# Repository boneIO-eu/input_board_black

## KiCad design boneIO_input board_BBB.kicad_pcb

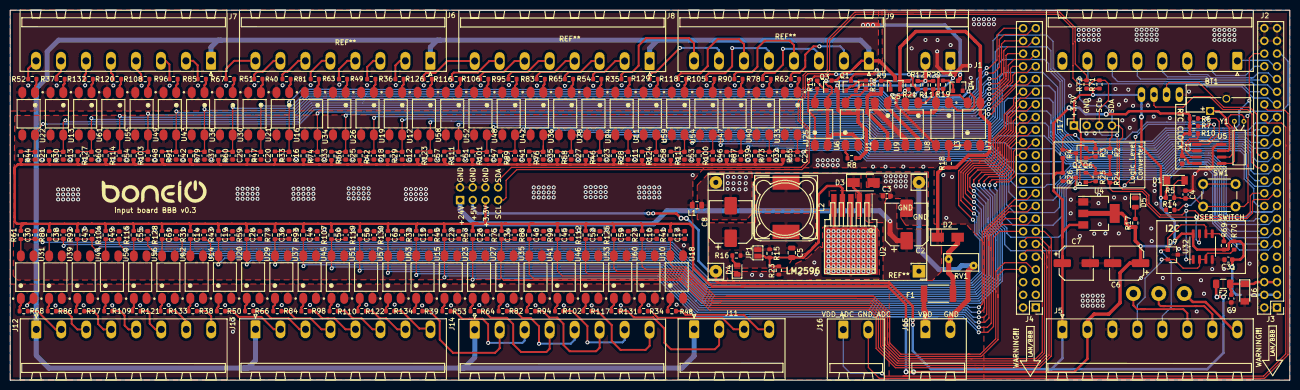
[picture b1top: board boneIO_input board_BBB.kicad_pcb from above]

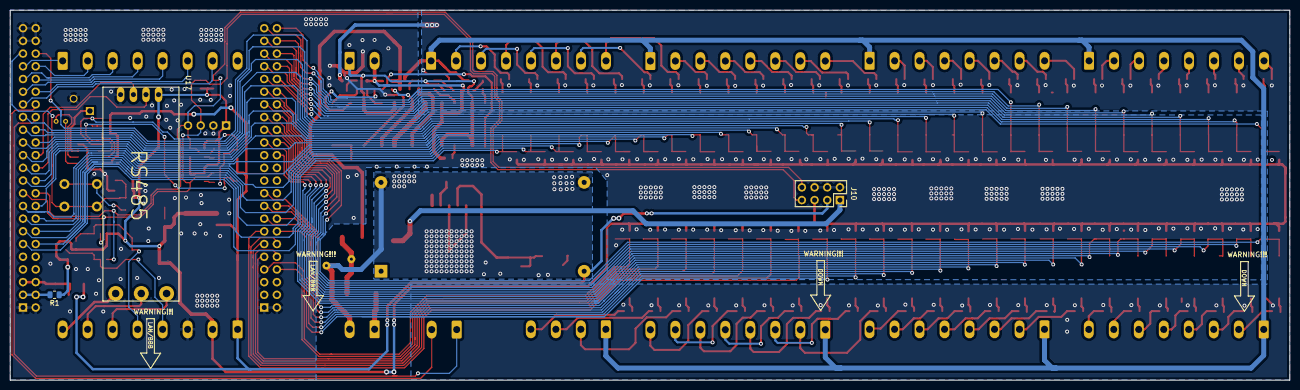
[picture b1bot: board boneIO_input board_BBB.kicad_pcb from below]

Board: 2 copper layers, 256.0 x 74.0 mm, 298 parts (3 on the bottom side), 215 nets.

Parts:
BT1: Battery; Battery_Panasonic_CR1220-VCN_Vertical_CircularHoles
C1, C4, C9, C10, C11, C12, C13, C14, C15, C16, C17, C18, C19, C20, C21, C22, C23, C24, C25, C26, C27, C28, C29, C30, C31, C32, C33, C34, C35, C36, C37, C38, C39, C40, C41, C42, C43, C44, C45, C46, C47, C48, C49, C50, C51, C52, C53, C54, C55, C56, C57, C58, C59, C60, C61, C62: 100n; C_0603_1608Metric
C2: 100uF/50V; CP_Elec_8x10
C3: 100n_NC; C_0603_1608Metric
C5: 3n3; C_0805_2012Metric
C6, C7: 100uF/16V; CP_Elec_6.3x5.4
C8: 220u/35V; CP_Elec_8x10
D1: 1N4148; D_MiniMELF
D2, D3: SS34; D_SMA
D4: LED_RED_NC; LED_0805_2012Metric
D5: LED_RED; LED_0805_2012Metric
D6: 5V6; D_MiniMELF
D7: BAT54A; SOT-23
F1: Fuse_3A; Fuse_2512_6332Metric
F2: 500mA; Fuse_1206_3216Metric
J1: EXT_PSU; PhoenixContact_MSTBA_2,5_2-G_1x02_P5.00mm_Horizontal
J2, J5, J6, J7, J8, J9, J12, J13, J14: Screw_Terminal_01x08; 8pin
J3, J4: BeagleBone_Black_Header; PinHeader_2x23_P2.54mm_Vertical
J10: Conn_02x04_Odd_Even; PinSocket_2x04_P2.54mm_Vertical
J11: Screw_Terminal_01x04; Phoenix_1x04_P5.00mm_Horizontal
J15, J16: Screw_Terminal_01x02; Phoenix_1x02_P5.00mm_Horizontal
J17: OLED; PinSocket_1x04_P2.54mm_Vertical
JP1: 5V; SolderJumper-2_P1.3mm_Open_Pad1.0x1.5mm
L1: BLM21PG221SN1D; L_0805_2012Metric
L2: 4.7uH; L_12x12mm_H6mm
Q1, Q4: BC817; SOT-23
Q2, Q6: BSS138; SOT-23
Q3, Q5: BC807; SOT-23
R1: 0k_NC; R_0805_2012Metric
R2, R3, R4, R5, R6, R7, R24, R25, R26, R34, R35, R36, R37, R38, R39, R40, R48, R49, R50, R51, R52, R53, R54, R62, R63, R64, R65, R66, R67, R68, R71, R72, R78, R81, R82, R83, R84, R85, R86, R90, R94, R95, R96, R97, R98, R102, R105, R106, R108, R109, R110, R116, R117, R118, R120, R121, R122, R126, R129, R131, R132, R133, R134: 4.7k; R_0603_1608Metric
R8, R9, R10, R11, R12, R13, R18, R19, R20, R21, R22, R27, R28, R29, R30, R31, R32, R41, R42, R43, R44, R45, R46, R55, R56, R57, R58, R59, R60, R61, R73, R74, R75, R76, R77, R79, R80, R87, R88, R89, R91, R92, R93, R99, R100, R101, R103, R104, R107, R111, R112, R113, R114, R115, R119, R123, R124, R125, R127, R128, R130: 10k; R_0603_1608Metric
R14: 330R; R_0603_1608Metric
R15: 3k; R_0603_1608Metric
R16: 1.2k; R_0603_1608Metric
R17: 1k; R_0603_1608Metric
R23: 1k_NC; R_0603_1608Metric
R33, R47: 10k_NC; R_0603_1608Metric
R69, R70: 680R; R_0603_1608Metric
RV1: 07D270K; RV_Disc_D7mm_W3.5mm_P5mm
SW1: SW_Push; SW_PUSH_6mm_H13mm
U1, U3, U6, U7, U8, U9, U10, U11, U12, U13, U14, U15, U16, U18, U19, U20, U21, U22, U23, U24, U25, U26, U27, U28, U29, U30, U31, U33, U34, U35, U36, U37, U38, U39, U40, U41, U42, U43, U44, U45, U46, U47, U48, U49, U50, U51, U52, U53, U54, U55, U56, U57, U58, U59, U60, U61, U62, U63: PC817X2NIP0F; SOT254P975X400-4N
U2: LM2596S-ADJ; TO-263-5_TabPin3
U4: AMS1117-3.3; SOT-223-3_TabPin2
U5: DS1307Z+; SOIC-8_3.9x4.9mm_P1.27mm
U17: RS485; RS485_moduleTTL
U32: P82B96; SO-8_3.9x4.9mm_P1.27mm
Y1: 32,788 MHz; Crystal_C26-LF_D2.1mm_L6.5mm_Horizontal

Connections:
+3V3: C6.1, C31.1, D1.1, J5.2, J10.5, J17.1, R1.1, R2.1, R3.1, R5.1, R17.1, R24.1, R25.1, R27.2, R28.2, R29.2, R30.2, R31.2, R32.2, R33.2, R41.2, R42.2, R43.2, R44.2, R45.2, R46.2, R47.2, R55.2, R56.2, R57.2, R58.2, R59.2, R60.2, R61.2, R69.1, R70.1, R71.1, R72.1, R73.2, R74.2, R75.2, R76.2, R77.2, R79.2, R80.2, R87.2, R88.2, R89.2, R91.2, R92.2, R93.2, R99.2, R100.2, R101.2, R103.2, R104.2, R107.2, R111.2, R112.2, R113.2, R114.2, R115.2, R119.2, R123.2, R124.2, R125.2, R127.2, R128.2, R130.2, U4.2, U17.1, U32.8
+5V: C1.1, C5.1, C7.1, C8.1, F2.2, J5.1, J10.3, JP1.2, L2.2, R4.1, R6.1, R7.1, R10.1, R15.1, R16.1, R26.1, U4.3, U5.8
+24V: C2.1, C3.1, D2.1, J10.1, Q5.2, R18.1, R21.1, U2.1, U7.3
+48V: J1.2, Q3.2, R8.1, R11.1, R12.1, R20.1, U1.3
A+: J5.6, U17.5
B-: J5.7, U17.6
Earth: C2.2, C3.2, C8.2, D3.2, D4.1, J15.2, L1.1, R23.2, RV1.2, U2.3, U2.5
GND: BT1.2, C1.2, C4.2, C6.2, C7.2, C9.2, C10.2, C11.2, C12.2, C13.2, C14.2, C15.2, C16.2, C17.2, C18.2, C19.2, C20.2, C21.2, C22.2, C23.2, C24.2, C25.2, C26.2, C27.2, C28.2, C29.2, C30.2, C31.2, C32.2, C33.2, C34.2, C35.2, C36.2, C37.2, C38.2, C39.2, C40.2, C41.2, C42.2, C43.2, C44.2, C45.2, C46.2, C47.2, C48.2, C49.2, C50.2, C51.2, C52.2, C53.2, C54.2, C55.2, C56.2, C57.2, C58.2, C59.2, C60.2, C61.2, C62.2, D5.1, D6.2, D7.3, J3.1, J3.2, J3.43, J3.44, J3.45, J3.46, J4.1, J4.2, J5.3, J10.2, J10.4, J10.6, J17.2, L1.2, Q4.2, R14.2, U3.3, U4.1, U5.4, U7.2, U8.3, U9.2, U9.3, U10.3, U11.3, U12.3, U13.3, U14.3, U15.3, U16.3, U17.4, U18.3, U19.3, U20.3, U21.3, U22.3, U23.3, U24.3, U25.3, U26.3, U27.3, U28.3, U29.3, U30.3, U31.3, U32.4, U33.3, U34.3, U35.3, U36.3, U37.3, U38.3, U39.3, U40.3, U41.3, U42.3, U43.3, U44.3, U45.3, U46.3, U47.3, U48.3, U49.3, U50.3, U51.3, U52.3, U53.3, U54.3, U55.3, U56.3, U57.3, U58.3, U59.3, U60.3, U61.3, U62.3, U63.3
GND1: J1.1, Q1.2, U1.2, U3.2, U6.2, U6.3, U8.2
GND2: J5.8, U17.7
GNDA: Q1.3, Q4.3, U10.2, U11.2, U12.2, U13.2, U14.2, U15.2, U16.2, U18.2, U19.2, U20.2, U21.2, U22.2, U23.2, U24.2, U25.2, U26.2, U27.2, U28.2, U29.2, U30.2, U31.2, U33.2, U34.2, U35.2, U36.2, U37.2, U38.2, U39.2, U40.2, U41.2, U42.2, U43.2, U44.2, U45.2, U46.2, U47.2, U48.2, U49.2, U50.2, U51.2, U52.2, U53.2, U54.2, U55.2, U56.2, U57.2, U58.2, U59.2, U60.2, U61.2, U62.2, U63.2
GND_ADC: J3.34, J16.2
unnamed: BT1.1, U5.3
unnamed: C5.2, JP1.1, R15.2, R23.1, U2.4
unnamed: C9.1, D6.1, F2.1, J3.5, J3.6
unnamed: D2.2, F1.1, RV1.1
unnamed: D3.1, L2.1, U2.2
unnamed: D4.2, R16.2
unnamed: D5.2, R17.2
unnamed: J3.3, J3.4, R1.2
unnamed: Q1.1, R9.2
unnamed: Q2.1, R3.2
unnamed: Q3.1, R13.2
unnamed: Q4.1, R19.2
unnamed: Q5.1, R22.2
unnamed: Q6.1, R25.2
unnamed: R8.2, U1.1
unnamed: R9.1, U1.4
unnamed: R10.2, U5.7
unnamed: R11.2, U3.1
unnamed: R12.2, U6.1
unnamed: R13.1, U6.4
unnamed: R14.1, SW1.1
unnamed: R18.2, U3.4, U7.1
unnamed: R19.1, U7.4
unnamed: R20.2, U8.1
unnamed: R21.2, U8.4, U9.1
unnamed: R22.1, U9.4
unnamed: R34.1, U10.1
unnamed: R35.1, U11.1
unnamed: R36.1, U12.1
unnamed: R37.1, U13.1
unnamed: R38.1, U14.1
unnamed: R39.1, U15.1
unnamed: R40.1, U16.1
unnamed: R48.1, U18.1
unnamed: R49.1, U19.1
unnamed: R50.1, U20.1
unnamed: R51.1, U21.1
unnamed: R52.1, U22.1
unnamed: R53.1, U23.1
unnamed: R54.1, U24.1
unnamed: R62.1, U25.1
unnamed: R63.1, U26.1
unnamed: R64.1, U27.1
unnamed: R65.1, U28.1
unnamed: R66.1, U29.1
unnamed: R67.1, U30.1
unnamed: R68.1, U31.1
unnamed: R78.1, U33.1
unnamed: R81.1, U34.1
unnamed: R82.1, U35.1
unnamed: R83.1, U36.1
unnamed: R84.1, U37.1
unnamed: R85.1, U38.1
unnamed: R86.1, U39.1
unnamed: R90.1, U40.1
unnamed: R94.1, U41.1
unnamed: R95.1, U42.1
unnamed: R96.1, U43.1
unnamed: R97.1, U44.1
unnamed: R98.1, U45.1
unnamed: R102.1, U46.1
unnamed: R105.1, U47.1
unnamed: R106.1, U48.1
unnamed: R108.1, U49.1
unnamed: R109.1, U50.1
unnamed: R110.1, U51.1
unnamed: R116.1, U52.1
unnamed: R117.1, U53.1
unnamed: R118.1, U54.1
unnamed: R120.1, U55.1
unnamed: R121.1, U56.1
unnamed: R122.1, U57.1
unnamed: R126.1, U58.1
unnamed: R129.1, U59.1
unnamed: R131.1, U60.1
unnamed: R132.1, U61.1
unnamed: R133.1, U62.1
unnamed: R134.1, U63.1
unnamed: U5.1, Y1.1
unnamed: U5.2, Y1.2
P8.07: C17.1, J4.7, R41.1, U18.4
P8.07_OUT: J11.4, R48.2
P8.08: C10.1, J4.8, R27.1, U10.4
P8.08_OUT: J11.3, R34.2
P8.09: C59.1, J4.9, R125.1, U60.4
P8.09_OUT: J11.2, R131.2
P8.10: C52.1, J4.10, R112.1, U53.4
P8.10_OUT: J14.8, R117.2
P8.11: C45.1, J4.11, R99.1, U46.4
P8.11_OUT: J14.7, R102.2
P8.12: C40.1, J4.12, R88.1, U41.4
P8.12_OUT: J14.6, R94.2
P8.13: C34.1, J4.13, R75.1, U35.4
P8.13_OUT: J14.5, R82.2
P8.14: C26.1, J4.14, R57.1, U27.4
P8.14_OUT: J14.4, R64.2
P8.15: C22.1, J4.15, R45.1, U23.4
P8.15_OUT: J14.3, R53.2
P8.16: C15.1, J4.16, R32.1, U15.4
P8.16_OUT: J14.2, R39.2
P8.17: C62.1, J4.17, R130.1, U63.4
P8.17_OUT: J13.8, R134.2
P8.18: C56.1, J4.18, R119.1, U57.4
P8.18_OUT: J13.7, R122.2
P8.19: C50.1, J4.19, R107.1, U51.4
P8.19_OUT: J13.6, R110.2
P8.26: C44.1, J4.26, R93.1, U45.4
P8.26_OUT: J13.5, R98.2
P8.27: C36.1, J4.27, R77.1, U37.4
P8.27_OUT: J13.4, R84.2
P8.28: C28.1, J4.28, R59.1, U29.4
P8.28_OUT: J13.3, R66.2
P8.29: C19.1, J4.29, R43.1, U20.4
P8.29_OUT: J13.2, R50.2
P8.30: C14.1, J4.30, R31.1, U14.4
P8.30_OUT: J12.8, R38.2
P8.31: C61.1, J4.31, R128.1, U62.4
P8.31_OUT: J12.7, R133.2
P8.32: C55.1, J4.32, R115.1, U56.4
P8.32_OUT: J12.6, R121.2
P8.33: C49.1, J4.33, R104.1, U50.4
P8.33_OUT: J12.5, R109.2
P8.34: C43.1, J4.34, R92.1, U44.4
P8.34_OUT: J12.4, R97.2
P8.35: C38.1, J4.35, R80.1, U39.4
P8.35_OUT: J12.3, R86.2
P8.36: C30.1, J4.36, R61.1, U31.4
P8.36_OUT: J12.2, R68.2
P8.37: C21.1, J4.37, R44.1, U22.4
P8.37_OUT: J7.8, R52.2
P8.38: C13.1, J4.38, R30.1, U13.4
P8.38_OUT: J7.7, R37.2
P8.39: C60.1, J4.39, R127.1, U61.4
P8.39_OUT: J7.6, R132.2
P8.40: C54.1, J4.40, R114.1, U55.4
P8.40_OUT: J7.5, R120.2
P8.41: C48.1, J4.41, R103.1, U49.4
P8.41_OUT: J7.4, R108.2
P8.42: C42.1, J4.42, R91.1, U43.4
P8.42_OUT: J7.3, R96.2
P8.43: C37.1, J4.43, R79.1, U38.4
P8.43_OUT: J7.2, R85.2
P8.44: C29.1, J4.44, R60.1, U30.4
P8.44_OUT: J6.8, R67.2
P8.45: C20.1, J4.45, R47.1, U21.4
P8.45_OUT: J6.7, R51.2
P8.46: C16.1, J4.46, R33.1, U16.4
P8.46_OUT: J6.6, R40.2
P9.11: C24.1, J3.11, R55.1, U25.4
P9.11_OUT: J9.2, R62.2
P9.12: C32.1, J3.12, R73.1, U33.4
P9.12_OUT: J9.3, R78.2
P9.13: C39.1, J3.13, R87.1, U40.4
P9.13_OUT: J9.4, R90.2
P9.14: C46.1, J3.14, R100.1, U47.4
P9.14_OUT: J9.5, R105.2
P9.15: C53.1, J3.15, R113.1, U54.4
P9.15_OUT: J9.6, R118.2
P9.16: C58.1, J3.16, R124.1, U59.4
P9.16_OUT: J9.7, R129.2
P9.17: C11.1, J3.17, R28.1, U11.4
P9.17_OUT: J9.8, R35.2
P9.18: C23.1, J3.18, R46.1, U24.4
P9.18_OUT: J8.2, R54.2
P9.21: C27.1, J3.21, R58.1, U28.4
P9.21_OUT: J8.3, R65.2
P9.22: C35.1, J3.22, R76.1, U36.4
P9.22_OUT: J8.4, R83.2
P9.23: C41.1, J3.23, R89.1, U42.4
P9.23_OUT: J8.5, R95.2
P9.25: C47.1, J3.25, R101.1, U48.4
P9.25_OUT: J8.6, R106.2
P9.27: C51.1, J3.27, R111.1, U52.4
P9.27_OUT: J8.7, R116.2
P9.28: C57.1, J3.28, R123.1, U58.4
P9.28_OUT: J8.8, R126.2
P9.29: C12.1, J3.29, R29.1, U12.4
P9.29_OUT: J6.2, R36.2
P9.30: C18.1, J3.30, R42.1, U19.4
P9.30_OUT: J6.3, R49.2
P9.31: C25.1, J3.31, R56.1, U26.4
P9.31_OUT: J6.4, R63.2
P9.33: J2.7, J3.33
P9.35: J2.5, J3.35
P9.36: J2.6, J3.36
P9.37: J2.3, J3.37
P9.38: J2.4, J3.38
P9.39: J2.1, J3.39
P9.40: J2.2, J3.40
P9.41: C4.1, D1.2, J3.41, R5.2, SW1.2
P9.42: C33.1, J3.42, R74.1, U34.4
P9.42_OUT: J6.5, R81.2
RX: J3.26, U17.3
SCL: J3.19, J10.7, J17.3, Q6.2, R24.2, R71.2, U32.7
SCL_5V: Q6.3, R7.2, R26.2, U5.6
SCL_OUT: D7.1, J5.5, R69.2, U32.5, U32.6
SDA: J3.20, J10.8, J17.4, Q2.2, R2.2, R72.2, U32.1
SDA_5V: Q2.3, R4.2, R6.2, U5.5
SDA_OUT: D7.2, J5.4, R70.2, U32.2, U32.3
TX: J3.24, U17.2
VCC: F1.2, J15.1
VDD: J6.1, J7.1, J8.1, J9.1, J11.1, J12.1, J13.1, J14.1, Q3.3, Q5.3
VDD_ADC: J3.32, J16.1

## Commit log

2021-12-18 update input_board_BBB v0.3
    update input_board_BBB v0.3
2021-12-18 corrected version
2021-12-18 corrected numbering
2021-12-18 removal of gerberas
2021-12-18 corrected J14
2022-01-16 Directory cleanup
2022-01-16 Create LICENSE
2022-02-24 input board v0.5
2022-03-05 input board v0.5a
2022-03-05 input_board_v0.5
2022-03-05 input board v0.5
    final version
2022-03-27 input board v0.4
    final version
2022-03-27 input_board_v0.4
    final version
    descriptions added
2022-05-03 input board v0.5 (4 Layers)
    Zmiany:
    - przejście z 2 na 4 warstwy
    - dodanie filtra dolnoprzepustowego na wszystkie inputy
    - dodanie RS485 na PCB
    - usunięcie DS2482+100
    _ dodanie rezystorów 0k do rozdzielenia GND
2022-07-07 first version input board v0.6
    Changes to the v0.6 version of the board:
    - 4 layer board
    - Change in schematic design
    - Removal of the XL1509 inverter
    - Installation of HLK-5D2405 isolated inverter ( galvic separation of GND and 5V)
    - Changes to the 3.3v inverter ( different capacitors)
2022-09-26 input board BBB v0.6
    ostateczna wersja
2022-09-27 input board v0.5 with 4 layers
2022-10-02 Final Version v0.6
    Design changes:
    - improving GND polygons
    Final version of the PCB
2024-02-17 input_board_v7.1
